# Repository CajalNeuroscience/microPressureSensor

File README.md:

# CN-1000 Microfluidic pressure sensor

## Motivation

We needed pressure monitoring within a microfluidic system to diagnose and monitor plumbing issues.  Finding the available units $$$, we set off to design our own. Like many good ideas, we aren't the first to try. 

Others have demonstrated the use of pressure sensors, originally designed for smart watches, as microfluidic pressure sensors:

https://www.hardware-x.com/article/S2468-0672(20)30021-3/fulltext

or depth sensors:

https://bluerobotics.com/store/sensors-sonars-cameras/sensors/bar30-sensor-r1/

This work largely replicates previous art with some ruggedization improvements. The resulting device uses generic communication protocols and does not require interfacing with a specific control or driver board to communicate with a PC.  Machined features for fittings support the pressure range of the transducer. Total cost per unit is under $200 USD. 

##  Mechanical

Pressure sensor assembly consists of completed PCB, housing block, and shim.  

The housing block CAD is available in ./CAD/Sensor block for 0.25-28 ports. This block accepts the assembled PCB and a inlet and outlet fluidics port.  These ports are made to accept 1/4"-28 flat-bottomed connectors for 1/8" OD tubing (ex: Idex part XP-335).  Material should be compatible with the solutions being used; parts machined from PEEK in Qty : 4 were $92 each from Quickparts. 

The shim piece holds the PCB and housing block at the appropriate spacing.  Without this shim it's easy to over-tighten the screws and destroy the pressure sensor component. The shim can be cut according to the included ./CAD/Sensor Block Shim.dxf file.  Cut this outline from just about any stable material of 0.8 mm (0.03") thickness. Prototypes used a piece of scrap laminated card. Suggested material is any stiff material of appropriate thickness that can be cut on a laser cutter (ex: McMaster-Carr 5751T11). 

Additional required hardware:

- Qty : 4 of 4-40 x 1/2" screws.  McMaster-Carr part 92949A110 or similar is OK. 
- Qty : 1 of sensor O-ring, 1.0 mm wide x 1.8 mm ID.  McMaster-Carr part 9262K112. 

For assembly, stack shim and PCB with shim hole over the pressure transducer base.  Install O-ring on pressure transducer barrel.  Insert the transducer and O-ring into the central hole of the housing block.  Take extra care to seat the O-ring where it will form a seal.  Install the 4-40 screws to secure the PCB and shim to the housing block.  When tightening, go slowly and tighten each screw in turn. 

The seal around the pressure transducer is critical for reliable readings.  It's common for this seal to be incomplete and allow air to leak around the O-ring. This effect is visible when monitoring readings from the pressure sensor during assembly.  With an assembled unit and the sensor readings visible in a real-time plotting window such as the Arduino Serial Plotter, squeezing the housing block at the two inlet ports will yield a spike in pressure.  If this pressure level holds as long as the block is squeezed, then the seal is good.  If this pressure spike decays quickly back down towards ambient pressure, there is a leak. Disassemble and reassemble the sensor and repeat the test. 

## Electrical 

Partlist

| Part | Value | Package | 
| ---- | ----- | ------- | 
|C1 | 100 nF | C1206 |
|J1 | QWIIC_RIGHT_ANGLE | JST04_1MM_RA |
|R1 | 10k | M1206 |
|R2 | 10k | M1206 |
|U1 | MS583730BA01-50 | TE_MS583730BA01-50 |

Pressure sensor is one of several related products from TE Connectivity.  The MS583730BA01-50 device was used here.  These are ~$14 on Digikey for Qty : 1.  Compatible products exist that have different pressure ranges and environment tolerances. 

Resistors both 10k pull-ups. Cap 100 nF power decoupling. All 1206 packages. 

Qwiic connectors make plugging between devices easy. Info here

https://www.sparkfun.com/qwiic

If you use the suggested QTPy board from Adafruit it includes the corresponding Qwiic connector.  There are many other alternatives for microcontrollers with the same connectors, as well as a number of other accessories.  Pick up a Qwiic cable to connect devices (https://www.sparkfun.com/products/17259 or similar). 

All parts are surface mount.  The pressure transducer is a fragile component and care must be taken in assembly.  Solder paste and a small hotplate (ex https://www.sainsmart.com/products/miniware-60w-mini-hot-plate-preheater-soldering-station) makes soldering the transducer straightforward.  The resistors and connector on the other side of the PCB can be soldered by hand. 

Included .brd file can be shared with your favorite PCB fab house. PCB from OSH Park was $3 each for Qty 3.

## Software

CN-1000 board natively supports i2c. If your application requries a USB connection, it's straightfoward to insert a microcontroller as a repeater/translator in line with the sensor.  

Suggested microcontroller is the QT Py from Adafruit (https://www.adafruit.com/qtpy) though nearly all modern microcontrollers support i2c and USB communication. This particular device includes a Qwiic connector for i2c, USB-C for serial comms and power, is fast, tiny, and cheap ($7.50 in Qty : 1).  The USB-C connection is plenty to power the microcontroller and sensor. These typically ship w/ circuitPython but support the Arduino IDE + C/C++ code just fine (https://learn.adafruit.com/adafruit-qt-py/using-with-arduino-ide).

Arduino-format firmware available in .\pressureSensor reads the sensor, then relays the pressure reading on a USB serial port. This works well with the Arduino Serial Plotter function if you'd like a live monitor of system pressure. 

Requires Blue Robotics MS5837 library, available through the Arduino IDE. In order to use this library the firmware code is written in C/C++.  

## Use

Files are available for non-commerical use.  If you would like to explore using this device commercially, please contact Cajal Neuroscience.

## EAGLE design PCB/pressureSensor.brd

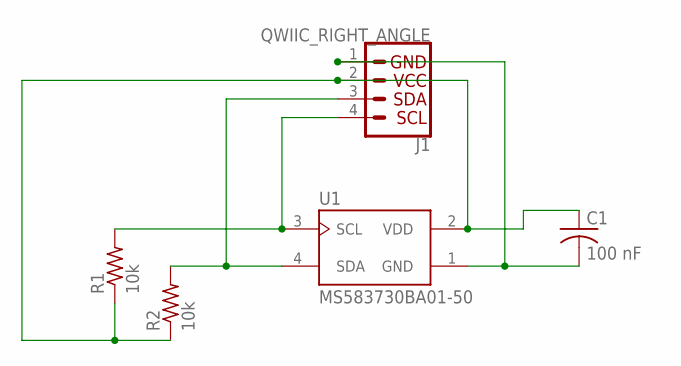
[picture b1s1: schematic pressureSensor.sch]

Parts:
C1: 100 nF; C1206
J1: QWIIC_RIGHT_ANGLE; JST04_1MM_RA
R1, R2: 10k; M1206
U1: MS583730BA01-50; TE_MS583730BA01-50

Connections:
GND: C1.2, J1.1, U1.1 (GND)
unnamed: J1.4, R1.2, U1.3 (SCL)
unnamed: C1.1, J1.2, R1.1, R2.1, U1.2 (VDD)
unnamed: J1.3, R2.2, U1.4 (SDA)

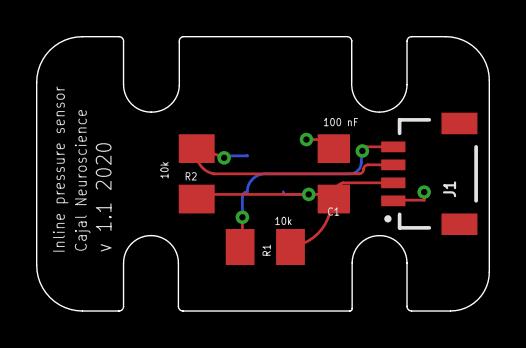
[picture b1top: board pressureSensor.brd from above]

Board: 2 copper layers, 25.1 x 15.2 mm, 5 parts (1 on the bottom side), 4 nets.

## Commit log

2022-04-29 Initial deposit of remote repo.
2022-04-29 Fussing with README formattting.:
2022-04-29 Fussing with README formatting.

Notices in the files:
parts and their libraries:
SparkFun-Connectors: Licensing: Creative Commons ShareAlike 4.0 International - https://creativecommons.org/licenses/by-sa/4.0
